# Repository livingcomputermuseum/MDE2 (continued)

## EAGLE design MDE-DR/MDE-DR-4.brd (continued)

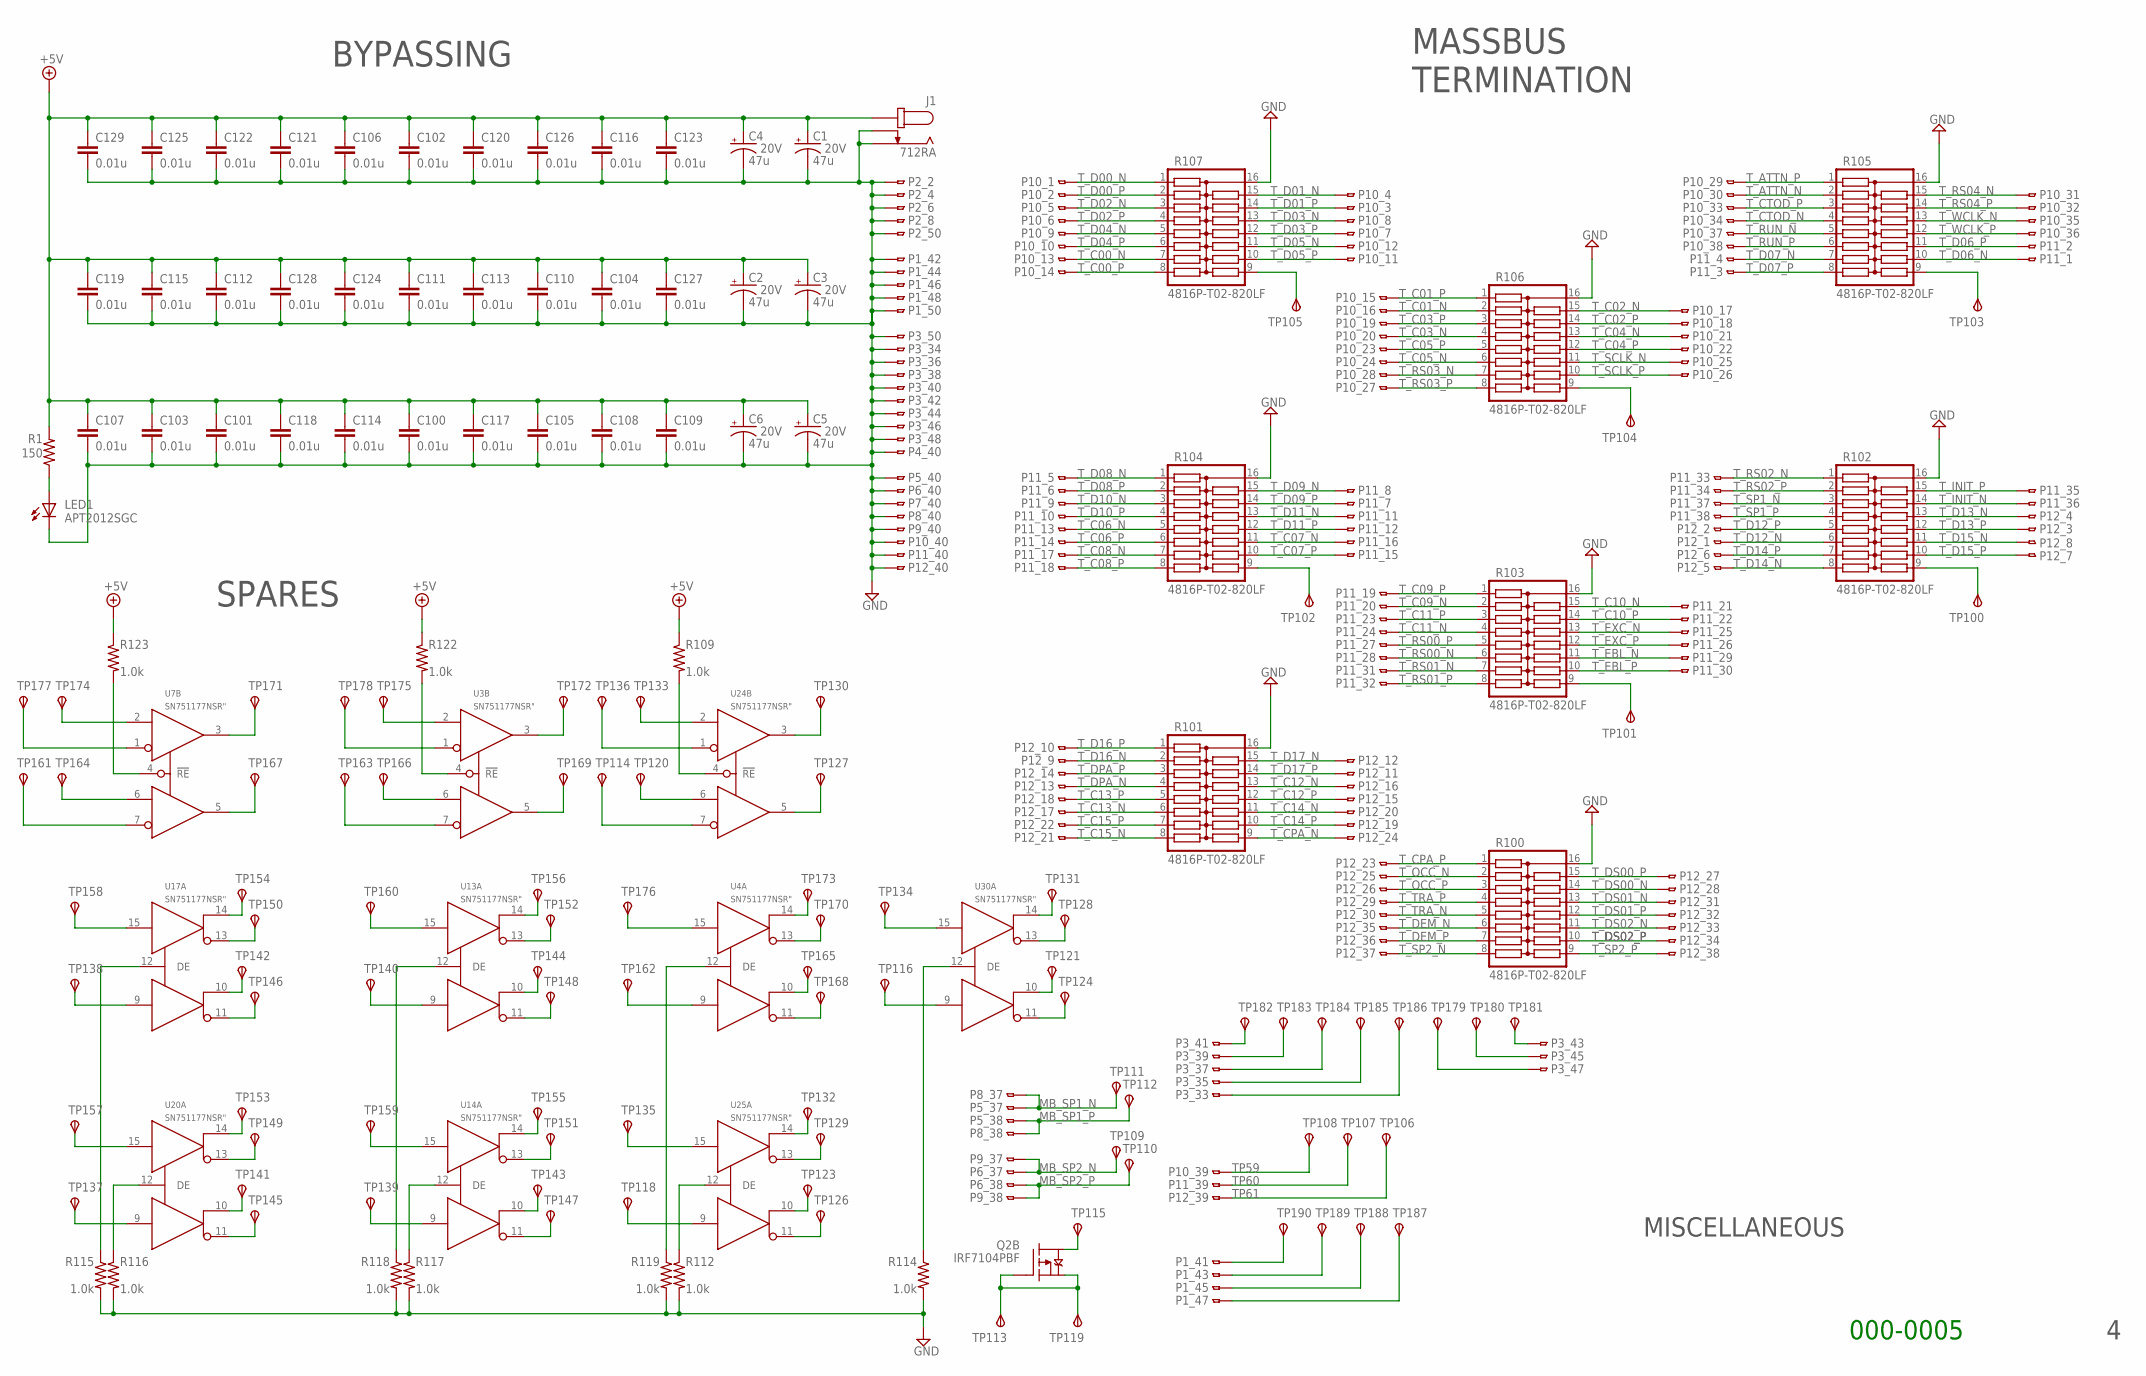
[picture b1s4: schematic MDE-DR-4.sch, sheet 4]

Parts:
C1, C2, C3, C4, C5, C6: 47u; C/6032-28R; VOLTAGE 20V
C100, C101, C102, C103, C104, C105, C106, C107, C108, C109, C110, C111, C112, C113, C114, C115, C116, C117, C118, C119, C120, C121, C122, C123, C124, C125, C126, C127, C128, C129: 0.01u; C0805K
J1: 712RA
LED1: APT2012SGC; SML0805
P1, P2, P3: CON50L
P4, P5, P6, P7, P8, P9, P10, P11, P12: CON40L
Q2: IRF7104PBF; SO-08
R1: 150; R0805
R100, R101, R102, R103, R104, R105, R106, R107: 4816P-T02-820LF; 4816P
R109, R112, R114, R115, R116, R117, R118, R119, R122, R123: 1.0k; R0805
TP100, TP101, TP102, TP103, TP104, TP105, TP106, TP107, TP108, TP109, TP110, TP111, TP112, TP113, TP114, TP115, TP116, TP118, TP119, TP120, TP121, TP123, TP124, TP126, TP127, TP128, TP129, TP130, TP131, TP132, TP133, TP134, TP135, TP136, TP137, TP138, TP139, TP140, TP141, TP142, TP143, TP144, TP145, TP146, TP147, TP148, TP149, TP150, TP151, TP152, TP153, TP154, TP155, TP156, TP157, TP158, TP159, TP160, TP161, TP162, TP163, TP164, TP165, TP166, TP167, TP168, TP169, TP170, TP171, TP172, TP173, TP174, TP175, TP176, TP177, TP178, TP179, TP180, TP181, TP182, TP183, TP184, TP185, TP186, TP187, TP188, TP189, TP190: TPSTP12R; TP12R
U3, U4, U7, U13, U14, U17, U20, U24, U25, U30: SN751177NSR"; SO16NS

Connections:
+5V: C1.+, C2.+, C3.+, C4.+, C5.+, C6.+, C100.1, C101.1, C102.1, C103.1, C104.1, C105.1, C106.1, C107.1, C108.1, C109.1, C110.1, C111.1, C112.1, C113.1, C114.1, C115.1, C116.1, C117.1, C118.1, C119.1, C120.1, C121.1, C122.1, C123.1, C124.1, C125.1, C126.1, C127.1, C128.1, C129.1, J1.PIN, R1.2, R109.1, R122.1, R123.1; also elsewhere on the board
GND: C1.-, C2.-, C3.-, C4.-, C5.-, C6.-, C100.2, C101.2, C102.2, C103.2, C104.2, C105.2, C106.2, C107.2, C108.2, C109.2, C110.2, C111.2, C112.2, C113.2, C114.2, C115.2, C116.2, C117.2, C118.2, C119.2, C120.2, C121.2, C122.2, C123.2, C124.2, C125.2, C126.2, C127.2, C128.2, C129.2, J1.SLEEVE, J1.SLEEVE_SHUNT, LED1.C, P1.42, P1.44, P1.46, P1.48, P1.50, P2.2, P2.4, P2.6, P2.8, P2.50, P3.34, P3.36, P3.38, P3.40, P3.42, P3.44, P3.46, P3.48, P3.50, P4.40, P5.40, P6.40, P7.40, P8.40, P9.40, P10.40, P11.40, P12.40, R100.16, R101.16, R102.16, R103.16, R104.16, R105.16, R106.16, R107.16, R112.2, R114.2, R115.2, R116.2, R117.2, R118.2, R119.2; also elsewhere on the board
MB_SP1_N: P5.37, P8.37, TP111.TP
MB_SP1_P: P5.38, P8.38, TP112.TP
MB_SP2_N: P6.37, P9.37, TP109.TP
MB_SP2_P: P6.38, P9.38, TP110.TP
unnamed: R119.1, U4.12 (DE)
unnamed: R112.1, U25.12 (DE)
unnamed: TP173.TP, U4.14 (1Y)
unnamed: TP138.TP, U17.9 (2D)
unnamed: TP158.TP, U17.15 (1D)
unnamed: TP157.TP, U20.15 (1D)
unnamed: TP137.TP, U20.9 (2D)
unnamed: TP160.TP, U13.15 (1D)
unnamed: TP140.TP, U13.9 (2D)
unnamed: TP176.TP, U4.15 (1D)
unnamed: TP162.TP, U4.9 (2D)
unnamed: TP135.TP, U25.15 (1D)
unnamed: TP118.TP, U25.9 (2D)
unnamed: TP139.TP, U14.9 (2D)
unnamed: TP159.TP, U14.15 (1D)
unnamed: TP154.TP, U17.14 (1Y)
unnamed: TP150.TP, U17.13 (!1Z)
unnamed: TP142.TP, U17.10 (2Y)
unnamed: TP146.TP, U17.11 (!2Z)
unnamed: TP156.TP, U13.14 (1Y)
unnamed: TP152.TP, U13.13 (!1Z)
unnamed: TP144.TP, U13.10 (2Y)
unnamed: TP148.TP, U13.11 (!2Z)
unnamed: TP155.TP, U14.14 (1Y)
unnamed: TP151.TP, U14.13 (!1Z)
unnamed: TP143.TP, U14.10 (2Y)
unnamed: TP147.TP, U14.11 (!2Z)
unnamed: TP132.TP, U25.14 (1Y)
unnamed: TP129.TP, U25.13 (!1Z)
unnamed: TP123.TP, U25.10 (2Y)
unnamed: TP126.TP, U25.11 (!2Z)
unnamed: TP165.TP, U4.10 (2Y)
unnamed: TP168.TP, U4.11 (!2Z)
unnamed: R117.1, U14.12 (DE)
unnamed: TP170.TP, U4.13 (!1Z)
unnamed: TP153.TP, U20.14 (1Y)
unnamed: TP149.TP, U20.13 (!1Z)
unnamed: TP141.TP, U20.10 (2Y)
unnamed: TP145.TP, U20.11 (!2Z)
unnamed: R118.1, U13.12 (DE)
unnamed: R116.1, U20.12 (DE)
unnamed: R115.1, U17.12 (DE)
unnamed: R114.1, U30.12 (DE)
unnamed: TP116.TP, U30.9 (2D)
unnamed: TP134.TP, U30.15 (1D)
unnamed: TP128.TP, U30.13 (!1Z)
unnamed: TP131.TP, U30.14 (1Y)
unnamed: TP121.TP, U30.10 (2Y)
unnamed: TP124.TP, U30.11 (!2Z)
unnamed: R107.9, TP105.TP
unnamed: R104.9, TP102.TP
unnamed: R106.9, TP104.TP
unnamed: R103.9, TP101.TP
unnamed: R105.9, TP103.TP
unnamed: Q2.3 (S), Q2.4 (G), TP113.TP, TP119.TP
unnamed: Q2.5 (D), Q2.6 (D), TP115.TP
unnamed: TP174.TP, U7.2 (1A)
unnamed: R102.9, TP100.TP
unnamed: TP177.TP, U7.1 (!1B)
unnamed: TP171.TP, U7.3 (1R)
unnamed: TP178.TP, U3.1 (!1B)
unnamed: TP175.TP, U3.2 (1A)
unnamed: TP172.TP, U3.3 (1R)
unnamed: TP164.TP, U7.6 (2A)
unnamed: TP161.TP, U7.7 (!2B)
unnamed: TP167.TP, U7.5 (2R)
unnamed: TP166.TP, U3.6 (2A)
unnamed: TP163.TP, U3.7 (!2B)
unnamed: TP169.TP, U3.5 (2R)
unnamed: R123.2, U7.4 (!RE)
unnamed: R122.2, U3.4 (!RE)
unnamed: TP133.TP, U24.2 (1A)
unnamed: TP136.TP, U24.1 (!1B)
unnamed: TP120.TP, U24.6 (2A)
unnamed: TP114.TP, U24.7 (!2B)
unnamed: TP130.TP, U24.3 (1R)
unnamed: TP127.TP, U24.5 (2R)
unnamed: R109.2, U24.4 (!RE)
unnamed: P1.41, TP190.TP
unnamed: P1.43, TP189.TP
unnamed: P1.45, TP188.TP
unnamed: P1.47, TP187.TP
unnamed: P3.41, TP182.TP
unnamed: P3.39, TP183.TP
unnamed: P3.37, TP184.TP
unnamed: P3.35, TP185.TP
unnamed: P3.33, TP186.TP
unnamed: P3.47, TP179.TP
unnamed: P3.45, TP180.TP
unnamed: P3.43, TP181.TP
unnamed: LED1.A, R1.1
TP59: P10.39, TP108.TP
TP60: P11.39, TP107.TP
TP61: P12.39, TP106.TP
T_ATTN_N: P10.30, R105.2
T_ATTN_P: P10.29, R105.1
T_C00_N: P10.13, R107.7
T_C00_P: P10.14, R107.8
T_C01_N: P10.16, R106.2
T_C01_P: P10.15, R106.1
T_C02_N: P10.17, R106.15
T_C02_P: P10.18, R106.14
T_C03_N: P10.20, R106.4
T_C03_P: P10.19, R106.3
T_C04_N: P10.21, R106.13
T_C04_P: P10.22, R106.12
T_C05_N: P10.24, R106.6
T_C05_P: P10.23, R106.5
T_C06_N: P11.13, R104.5
T_C06_P: P11.14, R104.6
T_C07_N: P11.16, R104.11
T_C07_P: P11.15, R104.10
T_C08_N: P11.17, R104.7
T_C08_P: P11.18, R104.8
T_C09_N: P11.20, R103.2
T_C09_P: P11.19, R103.1
T_C10_N: P11.21, R103.15
T_C10_P: P11.22, R103.14
T_C11_N: P11.24, R103.4
T_C11_P: P11.23, R103.3
T_C12_N: P12.16, R101.13
T_C12_P: P12.15, R101.12
T_C13_N: P12.17, R101.6
T_C13_P: P12.18, R101.5
T_C14_N: P12.20, R101.11
T_C14_P: P12.19, R101.10
T_C15_N: P12.21, R101.8
T_C15_P: P12.22, R101.7
T_CPA_N: P12.24, R101.9
T_CPA_P: P12.23, R100.1
T_CTOD_N: P10.34, R105.4
T_CTOD_P: P10.33, R105.3
T_D00_N: P10.1, R107.1
T_D00_P: P10.2, R107.2
T_D01_N: P10.4, R107.15
T_D01_P: P10.3, R107.14
T_D02_N: P10.5, R107.3
T_D02_P: P10.6, R107.4
T_D03_N: P10.8, R107.13
T_D03_P: P10.7, R107.12
T_D04_N: P10.9, R107.5
T_D04_P: P10.10, R107.6
T_D05_N: P10.12, R107.11
T_D05_P: P10.11, R107.10
T_D06_N: P11.1, R105.10
T_D06_P: P11.2, R105.11
T_D07_N: P11.4, R105.7
T_D07_P: P11.3, R105.8
T_D08_N: P11.5, R104.1
T_D08_P: P11.6, R104.2
T_D09_N: P11.8, R104.15
T_D09_P: P11.7, R104.14
T_D10_N: P11.9, R104.3
T_D10_P: P11.10, R104.4
T_D11_N: P11.11, R104.13
T_D11_P: P11.12, R104.12
T_D12_N: P12.1, R102.6
T_D12_P: P12.2, R102.5
T_D13_N: P12.4, R102.13
T_D13_P: P12.3, R102.12
T_D14_N: P12.5, R102.8
T_D14_P: P12.6, R102.7
T_D15_N: P12.8, R102.11
T_D15_P: P12.7, R102.10
T_D16_N: P12.9, R101.2
T_D16_P: P12.10, R101.1
T_D17_N: P12.12, R101.15
T_D17_P: P12.11, R101.14
T_DEM_N: P12.35, R100.6
T_DEM_P: P12.36, R100.7
T_DPA_N: P12.13, R101.4
T_DPA_P: P12.14, R101.3
T_DS00_N: P12.28, R100.14
T_DS00_P: P12.27, R100.15
T_DS01_N: P12.31, R100.13
T_DS01_P: P12.32, R100.12
T_DS02_N: P12.33, R100.11
T_DS02_P: P12.34, R100.10
T_EBL_N: P11.29, R103.11
T_EBL_P: P11.30, R103.10
T_EXC_N: P11.25, R103.13
T_EXC_P: P11.26, R103.12
T_INIT_N: P11.36, R102.14
T_INIT_P: P11.35, R102.15
T_OCC_N: P12.25, R100.2
T_OCC_P: P12.26, R100.3
T_RS00_N: P11.28, R103.6
T_RS00_P: P11.27, R103.5
T_RS01_N: P11.31, R103.7
T_RS01_P: P11.32, R103.8
T_RS02_N: P11.33, R102.1
T_RS02_P: P11.34, R102.2
T_RS03_N: P10.28, R106.7
T_RS03_P: P10.27, R106.8
T_RS04_N: P10.31, R105.15
T_RS04_P: P10.32, R105.14
T_RUN_N: P10.37, R105.5
T_RUN_P: P10.38, R105.6
T_SCLK_N: P10.25, R106.11
T_SCLK_P: P10.26, R106.10
T_SP1_N: P11.37, R102.3
T_SP1_P: P11.38, R102.4
T_SP2_N: P12.37, R100.8
T_SP2_P: P12.38, R100.9
T_TRA_N: P12.30, R100.5
T_TRA_P: P12.29, R100.4
T_WCLK_N: P10.35, R105.13
T_WCLK_P: P10.36, R105.12

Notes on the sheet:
MISCELLANEOUS
SPARES
MASSBUS TERMINATION
BYPASSING
000-0005

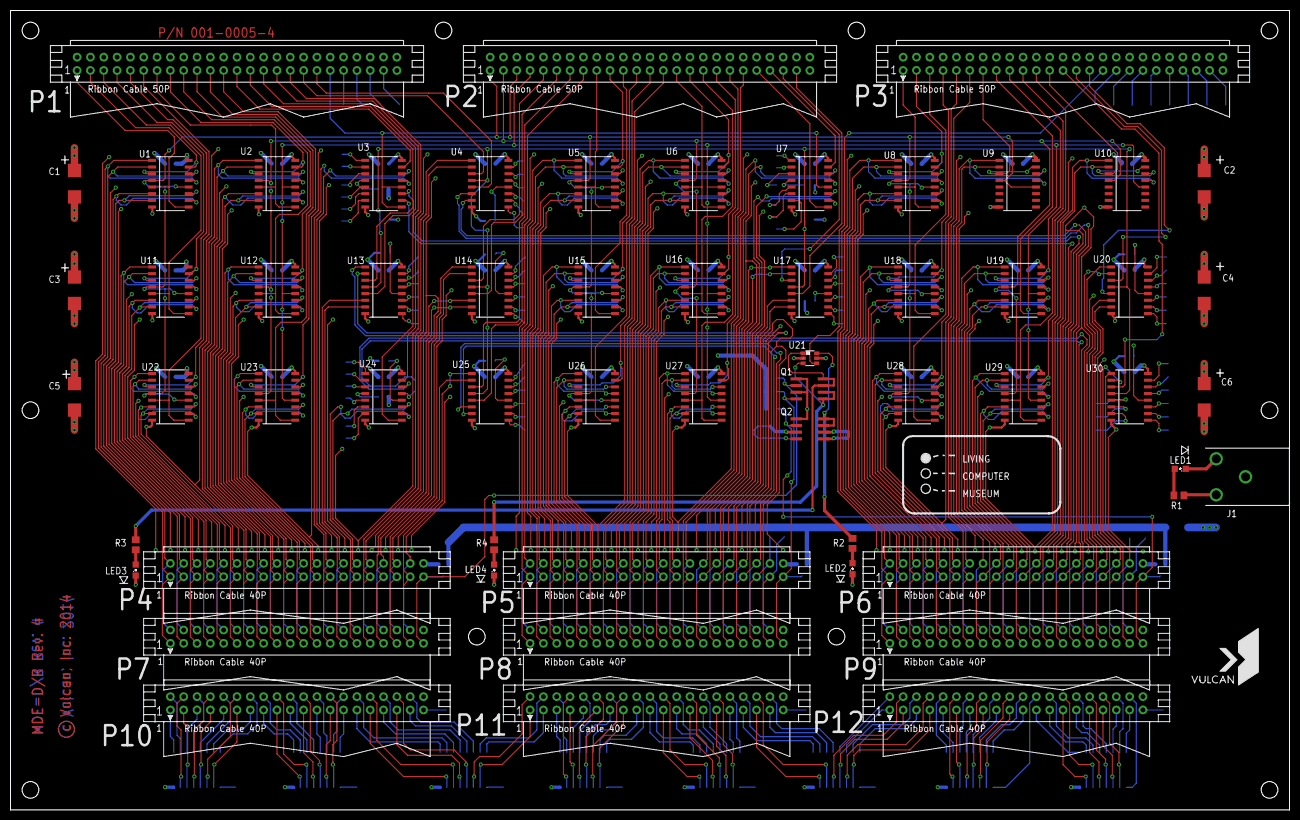
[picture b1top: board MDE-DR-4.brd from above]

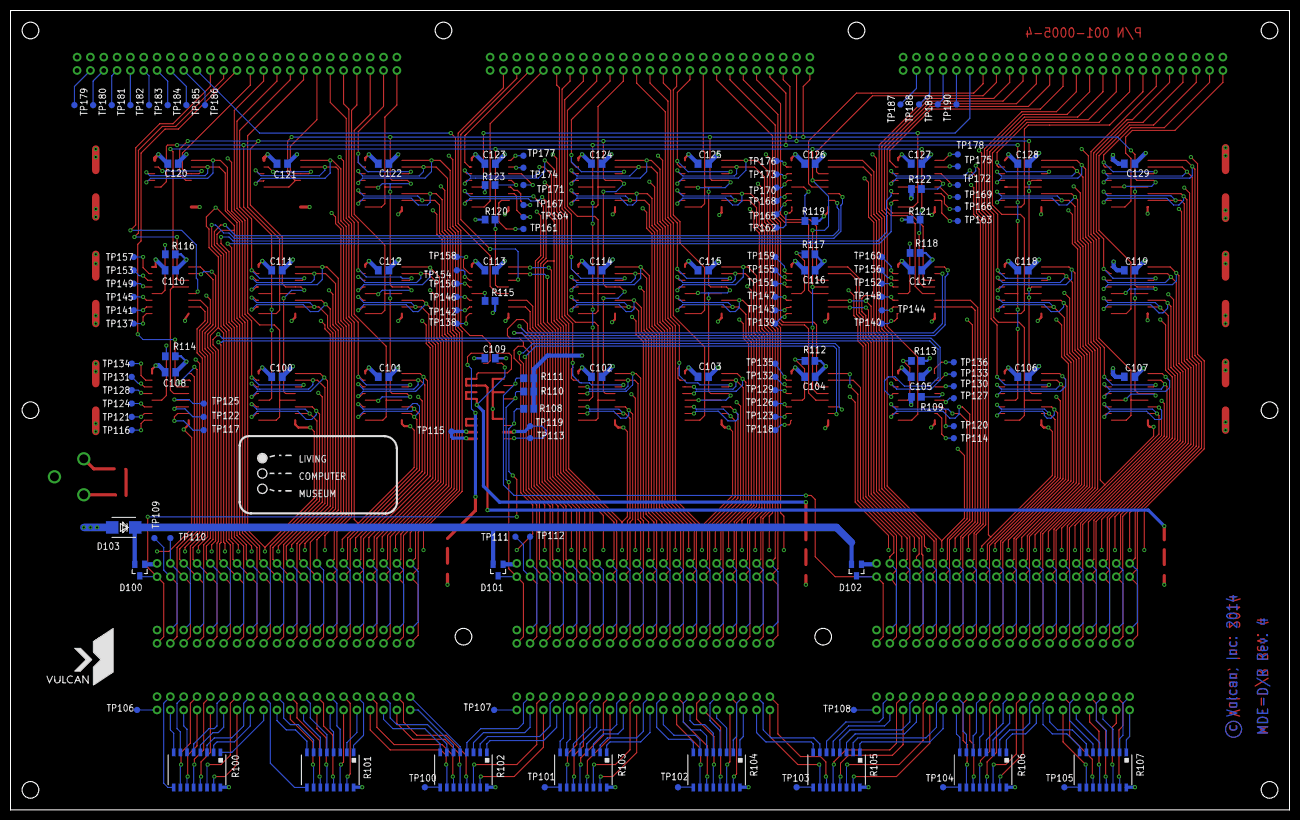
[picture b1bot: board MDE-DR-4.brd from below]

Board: 4 copper layers, 243.8 x 152.4 mm, 209 parts (149 on the bottom side), 398 nets.

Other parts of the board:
DRILEGEND: DRILEGEND

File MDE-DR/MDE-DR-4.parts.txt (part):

Partlist

Exported from MDE-DR-4.brd at 11/24/2014 12:50:32 PM

EAGLE Version 6.4.0 Copyright (c) 1988-2013 CadSoft

Assembly variant: 

Part     Value           Package       Library         Position (inch)       Orientation

C1       47u             C/6032-28R    rcl             (0.48 4.7)            R90
C2       47u             C/6032-28R    rcl             (8.96 4.7)            R90
C3       47u             C/6032-28R    rcl             (0.48 3.9)            R90
C4       47u             C/6032-28R    rcl             (8.96 3.9)            R90
C5       47u             C/6032-28R    rcl             (0.48 3.1)            R90
C6       47u             C/6032-28R    rcl             (8.96 3.1)            R90
C100     0.01u           C0805K        rcl             (7.6 3.25)            MR0
C101     0.01u           C0805K        rcl             (6.8 3.25)            MR0
C102     0.01u           C0805K        rcl             (5.2 3.25)            MR0
C103     0.01u           C0805K        rcl             (4.4 3.25)            MR0
C104     0.01u           C0805K        rcl             (3.6 3.25)            MR0
C105     0.01u           C0805K        rcl             (2.8 3.25)            MR0
C106     0.01u           C0805K        rcl             (2 3.25)              MR0
C107     0.01u           C0805K        rcl             (1.2 3.25)            MR0
C108     0.01u           C0805K        rcl             (8.4 3.285)           MR0
C109     0.01u           C0805K        rcl             (6 3.39)              MR0
C110     0.01u           C0805K        rcl             (8.4 4.05)            MR0
C111     0.01u           C0805K        rcl             (7.6 4.05)            MR0
C112     0.01u           C0805K        rcl             (6.8 4.05)            MR0
C113     0.01u           C0805K        rcl             (6 4.05)              MR0
C114     0.01u           C0805K        rcl             (5.2 4.05)            MR0
C115     0.01u           C0805K        rcl             (4.4 4.05)            MR0
C116     0.01u           C0805K        rcl             (3.6 4.05)            MR0
C117     0.01u           C0805K        rcl             (2.8 4.05)            MR0
C118     0.01u           C0805K        rcl             (2 4.05)              MR0
C119     0.01u           C0805K        rcl             (1.2 4.05)            MR0
C120     0.01u           C0805K        rcl             (8.38 4.85)           MR0
C121     0.01u           C0805K        rcl             (7.56 4.85)           MR0
C122     0.01u           C0805K        rcl             (6.8 4.85)            MR0
C123     0.01u           C0805K        rcl             (6 4.85)              MR0
C124     0.01u           C0805K        rcl             (5.2 4.85)            MR0
C125     0.01u           C0805K        rcl             (4.4 4.85)            MR0
C126     0.01u           C0805K        rcl             (3.6 4.85)            MR0
C127     0.01u           C0805K        rcl             (2.8 4.85)            MR0
C128     0.01u           C0805K        rcl             (2 4.85)              MR0
C129     0.01u           C0805K        rcl             (1.2 4.85)            MR0
D100     HSMS-2822       SOT23         diode           (8.63 1.8)            MR180
D101     HSMS-2822       SOT23         diode           (5.94 1.8)            MR180
D102     HSMS-2822       SOT23         diode           (3.25 1.8)            MR180
D103     1SMB5918BT3G    SMB           diode           (8.75 2.12)           MR180
J1       712RA           712RA         vulcan_custom   (9.05 2.5)            R180
LED1     APT2012SGC      SML0805       led             (8.78 2.56)           R180
LED2     APT2012EC       SML0805       led             (6.32 1.81)           R90
LED3     APT2012EC       SML0805       led             (0.94 1.8)            R90
LED4     APT2012EC       SML0805       led             (3.63 1.8)            R90
P1                       CON50L        vulcan_custom   (1.7 5.6)             R180
P2                       CON50L        vulcan_custom   (4.8 5.6)             R180
P3                       CON50L        vulcan_custom   (7.9 5.6)             R180
P4                       CON40L        vulcan_custom   (2.15 1.8)            R180
P5                       CON40L        vulcan_custom   (4.85 1.8)            R180
P6                       CON40L        vulcan_custom   (7.55 1.8)            R180
P7                       CON40L        vulcan_custom   (2.15 1.3)            R180
P8                       CON40L        vulcan_custom   (4.85 1.3)            R180
P9                       CON40L        vulcan_custom   (7.55 1.3)            R180
P10                      CON40L        vulcan_custom   (2.15 0.8)            R180
P11                      CON40L        vulcan_custom   (4.85 0.8)            R180
P12                      CON40L        vulcan_custom   (7.55 0.8)            R180
Q1       IRF7104PBF      SO-08         vulcan_custom   (6 3.16)              R270
Q2       IRF7104PBF      SO-08         vulcan_custom   (6 2.86)              R270
R1       150             R0805         rcl             (8.77 2.36)           R0
R2       150             R0805         rcl             (6.32 2)              R90
R3       150             R0805         rcl             (0.94 1.99)           R90
R4       150             R0805         rcl             (3.63 1.99)           R90
R100     4816P-T02-820LF 4816P         resistor-bourns (8.2 0.3)             MR180
R101     4816P-T02-820LF 4816P         resistor-bourns (7.2 0.3)             MR180
R102     4816P-T02-820LF 4816P         resistor-bourns (6.2 0.3)             MR180
R103     4816P-T02-820LF 4816P         resistor-bourns (5.3 0.3)             MR180
R104     4816P-T02-820LF 4816P         resistor-bourns (4.3 0.3)             MR180
R105     4816P-T02-820LF 4816P         resistor-bourns (3.4 0.3)             MR180
R106     4816P-T02-820LF 4816P         resistor-bourns (2.3 0.3)             MR180
R107     4816P-T02-820LF 4816P         resistor-bourns (1.4 0.3)             MR180
R108     10k             R0805         rcl             (5.71 3.01)           MR0
R109     1.0k            R0805         rcl             (2.8 3.1)             MR0
R110     10k             R0805         rcl             (5.71 3.14)           MR0
R111     10k             R0805         rcl             (5.71 3.24)           MR0
R112     1.0k            R0805         rcl             (3.6 3.37)            MR0
R113     1.0k            R0805         rcl             (2.8 3.37)            MR0
R114     1.0k            R0805         rcl             (8.4 3.405)           MR0
R115     1.0k            R0805         rcl             (6 3.82)              MR0
R116     1.0k            R0805         rcl             (8.4 4.17)            MR0
R117     1.0k            R0805         rcl             (3.6 4.17)            MR0
R118     1.0k            R0805         rcl             (2.81 4.18)           MR0
R119     1.0k            R0805         rcl             (3.6 4.42)            MR0
R120     1.0k            R0805         rcl             (6 4.43)              MR0
R121     1.0k            R0805         rcl             (2.81 4.43)           MR0
R122     1.0k            R0805         rcl             (2.8 4.66)            MR0
R123     1.0k            R0805         rcl             (6 4.69)              MR0
TP100    TPSTP12R        TP12R         testpad         (6.49 0.17)           MR0
TP101    TPSTP12R        TP12R         testpad         (5.59 0.17)           MR0
TP102    TPSTP12R        TP12R         testpad         (4.59 0.17)           MR0
TP103    TPSTP12R        TP12R         testpad         (3.7 0.17)            MR0
TP104    TPSTP12R        TP12R         testpad         (2.6 0.17)            MR0
TP105    TPSTP12R        TP12R         testpad         (1.69 0.17)           MR0
TP106    TPSTP12R        TP12R         testpad         (8.65 0.75)           MR0
TP107    TPSTP12R        TP12R         testpad         (5.97 0.75)           MR0
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
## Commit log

2017-12-08 Create LICENSE
2017-12-08 Updated copyright info
